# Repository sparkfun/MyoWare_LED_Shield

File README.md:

MyoWare™ LED Shield
========================================

[*MyoWare LED Shield (13688)*](https://www.sparkfun.com/products/13688)

The MyoWare™ LED Shield is designed to pair with the MyoWare™ Muscle Sensor. The 10 segment bar graph shows the magnitude of the measured signal.

Repository Contents
-------------------

* **/Hardware** - Eagle design files (.brd, .sch)

Documentation
--------------
* **[Hookup Guide](https://learn.sparkfun.com/tutorials/myoware-muscle-sensor-kit?_ga=1.172011619.1515819426.1457626448)** - Basic hookup guide for the MyoWare™ LED Shield.
* **[SparkFun Fritzing repo](https://github.com/sparkfun/Fritzing_Parts)** - Fritzing diagrams for SparkFun products.
* **[SparkFun 3D Model repo](https://github.com/sparkfun/3D_Models)** - 3D models of SparkFun products.

License Information
-------------------

This product is _**open source**_!

Please review the LICENSE.md file for license information.

If you have any questions or concerns on licensing, please contact techsupport@sparkfun.com.

Distributed as-is; no warranty is given.

- Your friends at SparkFun.

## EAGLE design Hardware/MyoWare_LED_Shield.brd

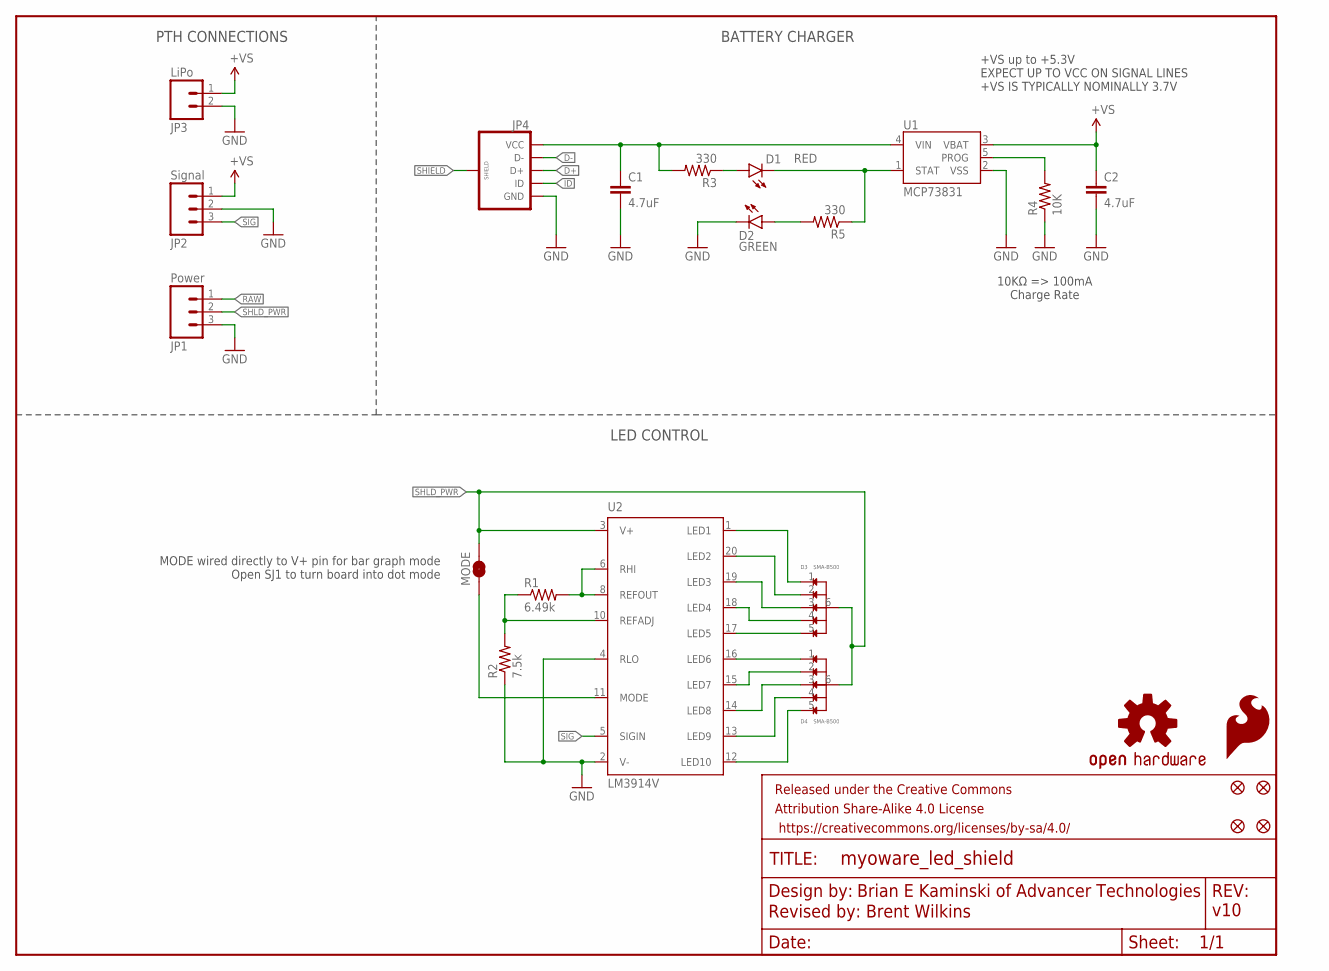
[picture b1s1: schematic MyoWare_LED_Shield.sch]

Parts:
C1, C2: 4.7uF; 0603-CAP
D1: RED; LED-0603
D2: GREEN; LED-0603
D3, D4: SMA-B500; LED_BAR_SMD
FID1, FID2, FID3, FID4: FIDUCIAL1X2; FIDUCIAL-1X2
FRAME1: FRAME-LETTER; CREATIVE_COMMONS
JP1: Power; 1X03_NO_SILK
JP2: Signal; 1X03_NO_SILK
JP3: LiPo; 1X02_NO_SILK
JP4: USB_MICROB_PLUGCONN-11752; USB-B-MICRO-SMD_V03
LOGO1: SFE_LOGO_FLAME.1_INCH; SFE_LOGO_FLAME_.1
LOGO2: OSHW-LOGOS; OSHW-LOGO-S
MODE: JUMPER-PAD-2-NC_BY_TRACE; PAD-JUMPER-2-NC_BY_TRACE_YES_SILK
R1: 6.49k; R0603
R2: 7.5k; R0603
R3, R5: 330; 0603-RES
R4: 10K; 0603-RES
U1: MCP73831; SOT23-5
U2: LM3914V; PLCC20S

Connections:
+VS: C2.1, JP2.1, JP3.1, U1.3 (VBAT)
D+: JP4.D+
D-: JP4.D-
GND: C1.2, C2.2, D2.C, JP1.3, JP2.2, JP3.2, JP4.GND, R2.1, R4.1, U1.2 (VSS), U2.2 (V-), U2.4 (RLO)
ID: JP4.ID
unnamed: D3.1, U2.1 (LED1)
unnamed: D3.2, U2.20 (LED2)
unnamed: D3.5, U2.17 (LED5)
unnamed: D3.3, U2.19 (LED3)
unnamed: D4.1, U2.16 (LED6)
unnamed: MODE.1, U2.11 (MODE)
unnamed: D3.4, U2.18 (LED4)
unnamed: D2.A, R5.2
unnamed: D1.A, R3.1
unnamed: D4.2, U2.15 (LED7)
unnamed: D4.3, U2.14 (LED8)
unnamed: D4.4, U2.13 (LED9)
unnamed: D4.5, U2.12 (LED10)
unnamed: D1.C, R5.1, U1.1 (STAT)
unnamed: R4.2, U1.5 (PROG)
unnamed: R1.1, R2.2, U2.10 (REFADJ)
unnamed: R1.2, U2.6 (RHI), U2.8 (REFOUT)
RAW: JP1.1
SHIELD: JP4.SHIELD1 (SHIELD), JP4.SHIELD2 (SHIELD), JP4.SHIELD3 (SHIELD)
SHLD_PWR: D3.6, D4.6, JP1.2, MODE.2, U2.3 (V+)
SIG: JP2.3, U2.5 (SIGIN)
VBUS: C1.1, JP4.VBUS (VCC), R3.2, U1.4 (VIN)

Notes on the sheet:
Brian E Kaminski of Advancer Technologies
Revised by: Brent Wilkins
v10
+VS up to +5.3V EXPECT UP TO VCC ON SIGNAL LINES +VS IS TYPICALLY NOMINALLY 3.7V
MODE wired directly to V+ pin for bar graph mode Open SJ1 to turn board into dot mode
PTH CONNECTIONS
BATTERY CHARGER
LED CONTROL
10KΩ => 100mA Charge Rate

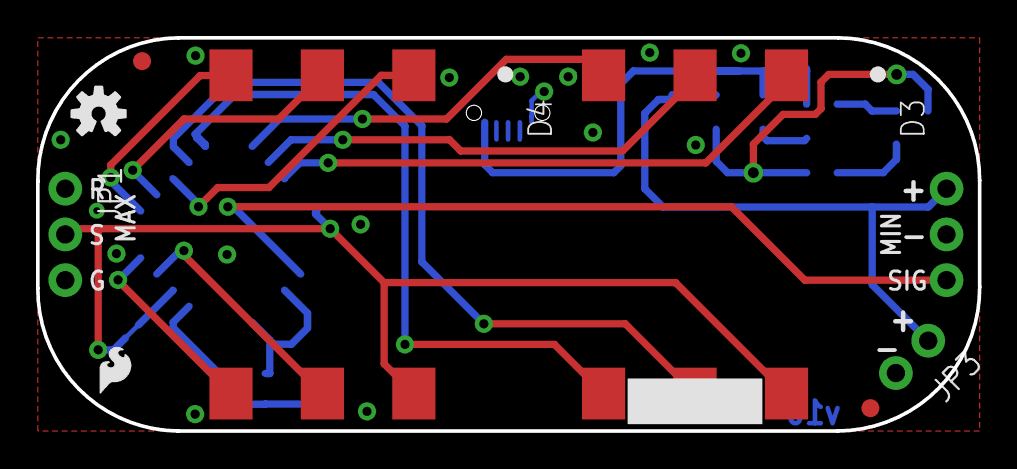
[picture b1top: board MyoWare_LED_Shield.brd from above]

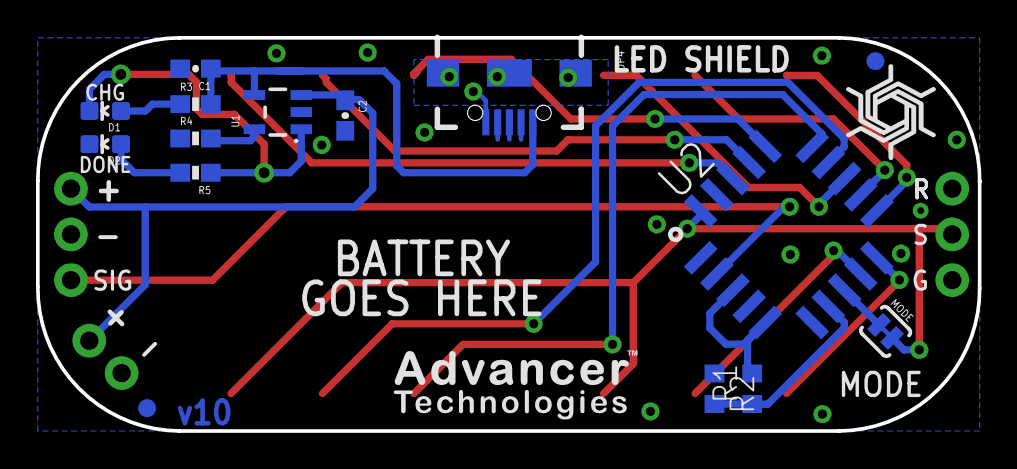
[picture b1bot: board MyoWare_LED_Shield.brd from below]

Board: 2 copper layers, 52.3 x 21.8 mm, 27 parts (17 on the bottom side), 23 nets.

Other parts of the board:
U$6: ADVANCER_LOGO
U$9: SPIRAL_LOGO_60%

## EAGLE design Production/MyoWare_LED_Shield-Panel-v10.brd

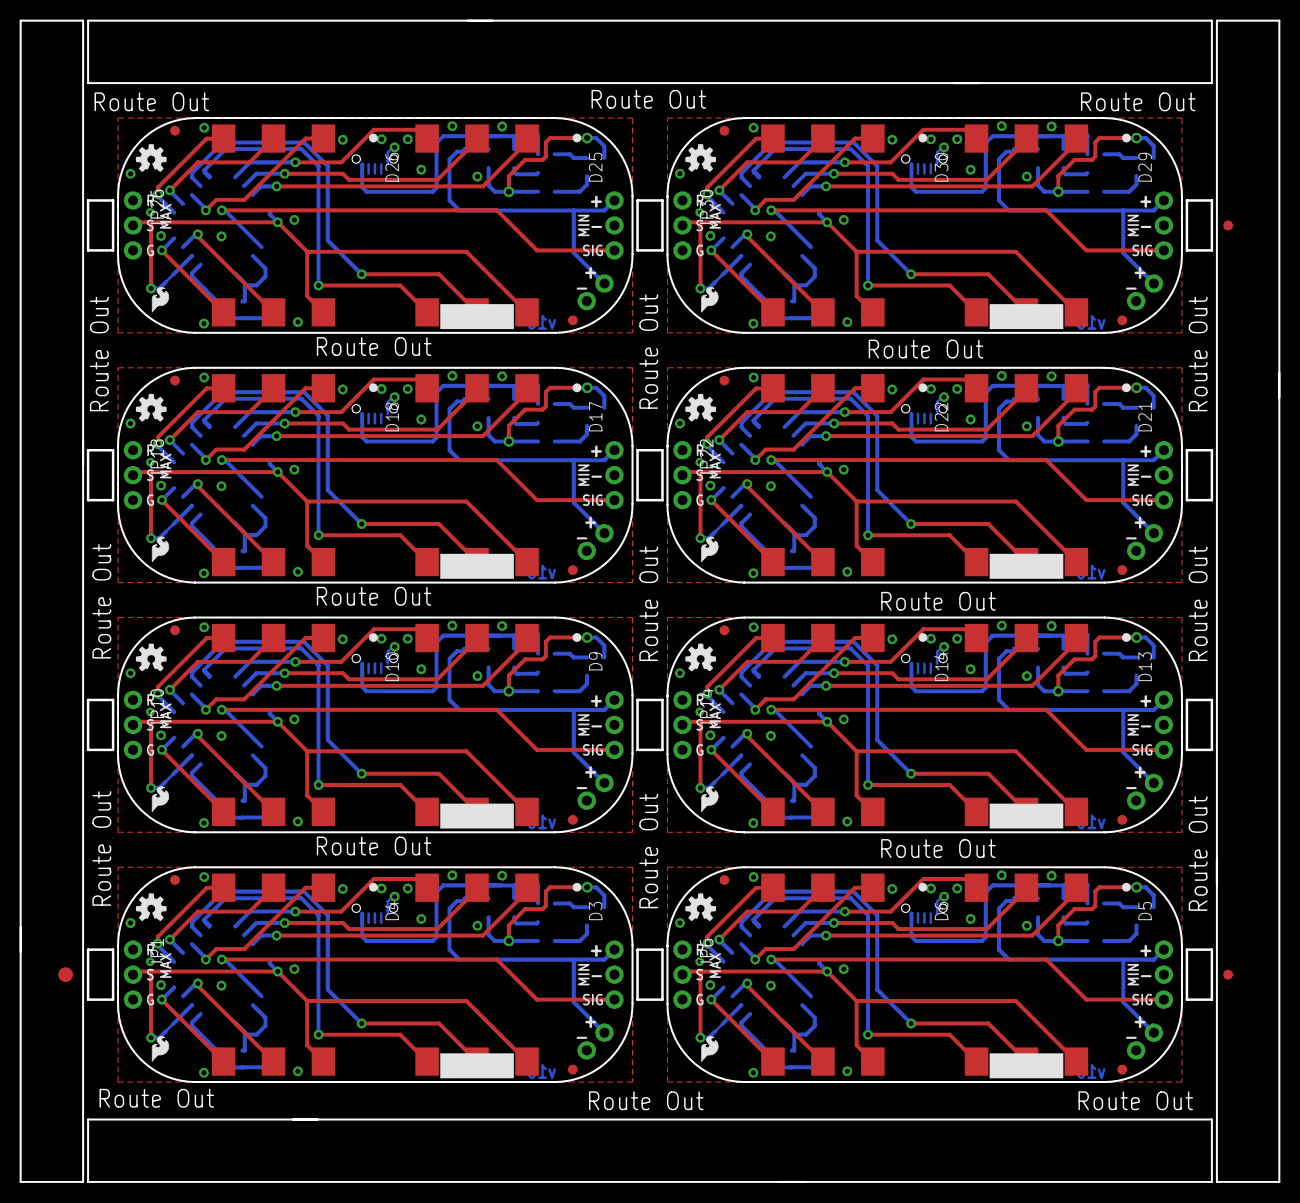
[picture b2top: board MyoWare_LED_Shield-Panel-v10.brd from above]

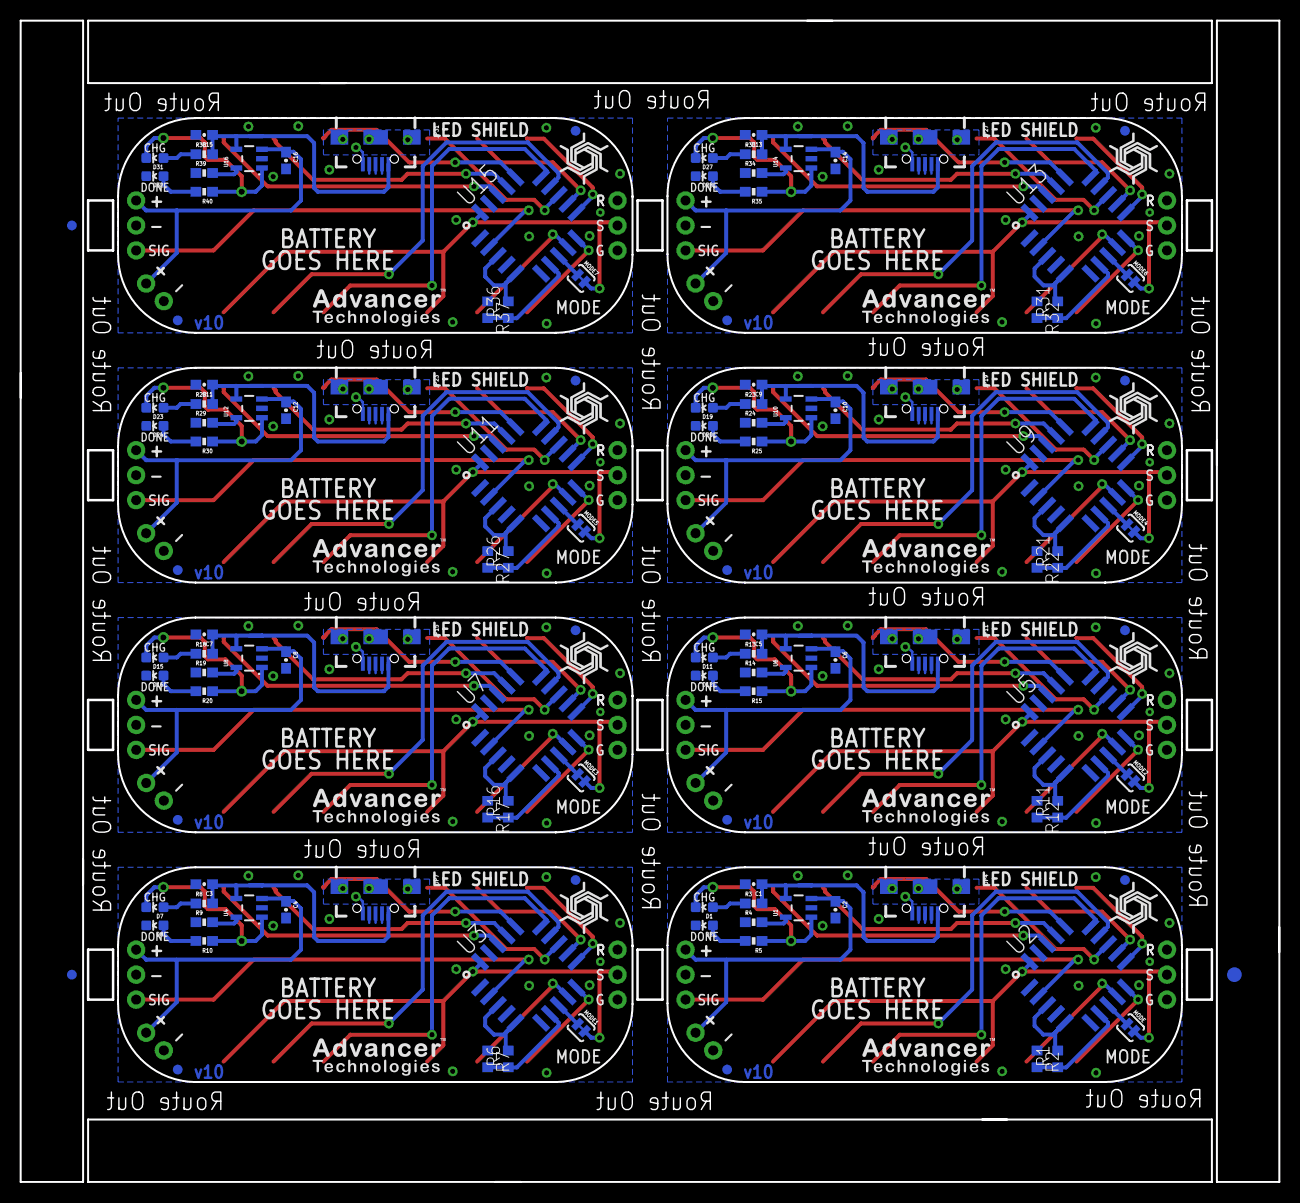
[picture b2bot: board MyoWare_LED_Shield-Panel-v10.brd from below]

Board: 2 copper layers, 128.0 x 118.1 mm, 214 parts (139 on the bottom side), 184 nets.

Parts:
C1, C2, C3, C4, C5, C6, C7, C8, C9, C10, C11, C12, C13, C14, C15, C16: 4.7uF; 0603-CAP
D1, D7, D11, D15, D19, D23, D27, D31: RED; LED-0603
D2, D8, D12, D16, D20, D24, D28, D32: GREEN; LED-0603
D3, D4, D5, D6, D9, D10, D13, D14, D17, D18, D21, D22, D25, D26, D29, D30: SMA-B500; LED_BAR_SMD
E$1, E$4: FIDUCIAL-1.5X3
E$2, E$3, E$5, E$6: FIDUCIAL-1X2
FID1, FID2, FID3, FID4, FID5, FID6, FID7, FID8, FID9, FID10, FID11, FID12, FID13, FID14, FID15, FID16, FID17, FID18, FID19, FID20, FID21, FID22, FID23, FID24, FID25, FID26, FID27, FID28, FID29, FID30, FID31, FID32: FIDUCIAL1X2; FIDUCIAL-1X2
JP1, JP6, JP10, JP14, JP18, JP22, JP26, JP30: Power; 1X03_NO_SILK
JP2, JP5, JP9, JP13, JP17, JP21, JP25, JP29: Signal; 1X03_NO_SILK
JP3, JP8, JP12, JP16, JP20, JP24, JP28, JP32: LiPo; 1X02_NO_SILK
JP4, JP7, JP11, JP15, JP19, JP23, JP27, JP31: USB-B-MICRO-SMD_V03
LOGO1, LOGO3, LOGO5, LOGO7, LOGO9, LOGO11, LOGO13, LOGO15: SFE_LOGO_FLAME.1_INCH; SFE_LOGO_FLAME_.1
LOGO2, LOGO4, LOGO6, LOGO8, LOGO10, LOGO12, LOGO14, LOGO16: OSHW-LOGOS; OSHW-LOGO-S
MODE, MODE1, MODE2, MODE3, MODE4, MODE5, MODE6, MODE7: JUMPER-PAD-2-NC_BY_TRACE; PAD-JUMPER-2-NC_BY_TRACE_YES_SILK
R1, R6, R11, R16, R21, R26, R31, R36: 6.49k; R0603
R2, R7, R12, R17, R22, R27, R32, R37: 7.5k; R0603
R3, R5, R8, R10, R13, R15, R18, R20, R23, R25, R28, R30, R33, R35, R38, R40: 330; 0603-RES
R4, R9, R14, R19, R24, R29, R34, R39: 10K; 0603-RES
U1, U4, U6, U8, U10, U12, U14, U16: MCP73831; SOT23-5
U2, U3, U5, U7, U9, U11, U13, U15: LM3914V; PLCC20S
U$1, U$3, U$5, U$8, U$9, U$11, U$13, U$15: SPIRAL_LOGO_60%
U$2, U$4, U$6, U$7, U$10, U$12, U$14, U$16: ADVANCER_LOGO

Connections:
+VS: C2.1, JP2.1, JP3.1, U1.3
+VS1: C4.1, JP5.1, JP8.1, U4.3
+VS2: C6.1, JP9.1, JP12.1, U6.3
+VS3: C8.1, JP13.1, JP16.1, U8.3
+VS4: C10.1, JP17.1, JP20.1, U10.3
+VS5: C12.1, JP21.1, JP24.1, U12.3
+VS6: C14.1, JP25.1, JP28.1, U14.3
+VS7: C16.1, JP29.1, JP32.1, U16.3
GND: C1.2, C2.2, D2.C, JP1.3, JP2.2, JP3.2, JP4.GND, R2.1, R4.1, U1.2, U2.2, U2.4
GND1: C3.2, C4.2, D8.C, JP5.2, JP6.3, JP7.GND, JP8.2, R7.1, R9.1, U3.2, U3.4, U4.2
GND2: C5.2, C6.2, D12.C, JP9.2, JP10.3, JP11.GND, JP12.2, R12.1, R14.1, U5.2, U5.4, U6.2
GND3: C7.2, C8.2, D16.C, JP13.2, JP14.3, JP15.GND, JP16.2, R17.1, R19.1, U7.2, U7.4, U8.2
GND4: C9.2, C10.2, D20.C, JP17.2, JP18.3, JP19.GND, JP20.2, R22.1, R24.1, U9.2, U9.4, U10.2
GND5: C11.2, C12.2, D24.C, JP21.2, JP22.3, JP23.GND, JP24.2, R27.1, R29.1, U11.2, U11.4, U12.2
GND6: C13.2, C14.2, D28.C, JP25.2, JP26.3, JP27.GND, JP28.2, R32.1, R34.1, U13.2, U13.4, U14.2
GND7: C15.2, C16.2, D32.C, JP29.2, JP30.3, JP31.GND, JP32.2, R37.1, R39.1, U15.2, U15.4, U16.2
unnamed: D3.1, U2.1
unnamed: D3.2, U2.20
unnamed: D3.5, U2.17
unnamed: D3.3, U2.19
unnamed: D4.1, U2.16
unnamed: MODE.1, U2.11
unnamed: D5.1, U3.1
unnamed: D3.4, U2.18
unnamed: D2.A, R5.2
unnamed: D1.A, R3.1
unnamed: D4.2, U2.15
unnamed: D4.3, U2.14
unnamed: D4.4, U2.13
unnamed: D4.5, U2.12
unnamed: D1.C, R5.1, U1.1
unnamed: D5.2, U3.20
unnamed: R4.2, U1.5
unnamed: D5.3, U3.19
unnamed: R1.1, R2.2, U2.10
unnamed: R1.2, U2.6, U2.8
unnamed: D5.4, U3.18
unnamed: D6.2, U3.15
unnamed: D6.3, U3.14
unnamed: D6.4, U3.13
unnamed: D6.5, U3.12
unnamed: R6.1, R7.2, U3.10
unnamed: R6.2, U3.6, U3.8
unnamed: D5.5, U3.17
unnamed: D6.1, U3.16
unnamed: MODE1.1, U3.11
unnamed: D7.A, R8.1
unnamed: D7.C, R10.1, U4.1
unnamed: R9.2, U4.5
unnamed: D8.A, R10.2
unnamed: D9.1, U5.1
unnamed: D9.2, U5.20
unnamed: D9.3, U5.19
unnamed: D9.4, U5.18
unnamed: D10.2, U5.15
unnamed: D10.3, U5.14
unnamed: D10.4, U5.13
unnamed: D10.5, U5.12
unnamed: R11.1, R12.2, U5.10
unnamed: R11.2, U5.6, U5.8
unnamed: D9.5, U5.17
unnamed: D10.1, U5.16
unnamed: MODE2.1, U5.11
unnamed: D11.A, R13.1
unnamed: D11.C, R15.1, U6.1
unnamed: R14.2, U6.5
unnamed: D12.A, R15.2
unnamed: D13.1, U7.1
unnamed: D13.2, U7.20
unnamed: D13.3, U7.19
unnamed: D13.4, U7.18
unnamed: D14.2, U7.15
unnamed: D14.3, U7.14
unnamed: D14.4, U7.13
unnamed: D14.5, U7.12
unnamed: R16.1, R17.2, U7.10
unnamed: R16.2, U7.6, U7.8
unnamed: D13.5, U7.17
unnamed: D14.1, U7.16
unnamed: MODE3.1, U7.11
unnamed: D15.A, R18.1
unnamed: D15.C, R20.1, U8.1
unnamed: R19.2, U8.5
unnamed: D16.A, R20.2
unnamed: D17.1, U9.1
unnamed: D17.2, U9.20
unnamed: D17.3, U9.19
unnamed: D17.4, U9.18
unnamed: D18.2, U9.15
unnamed: D18.3, U9.14
unnamed: D18.4, U9.13
unnamed: D18.5, U9.12
unnamed: R21.1, R22.2, U9.10
unnamed: R21.2, U9.6, U9.8
unnamed: D17.5, U9.17
unnamed: D18.1, U9.16
unnamed: MODE4.1, U9.11
unnamed: D19.A, R23.1
unnamed: D19.C, R25.1, U10.1
unnamed: R24.2, U10.5
unnamed: D20.A, R25.2
unnamed: D21.1, U11.1
unnamed: D21.2, U11.20
unnamed: D21.3, U11.19
unnamed: D21.4, U11.18
unnamed: D22.2, U11.15
unnamed: D22.3, U11.14
unnamed: D22.4, U11.13
unnamed: D22.5, U11.12
unnamed: R26.1, R27.2, U11.10
unnamed: R26.2, U11.6, U11.8
unnamed: D21.5, U11.17
unnamed: D22.1, U11.16
unnamed: MODE5.1, U11.11
unnamed: D23.A, R28.1
unnamed: D23.C, R30.1, U12.1
unnamed: R29.2, U12.5
unnamed: D24.A, R30.2
unnamed: D25.1, U13.1
unnamed: D25.2, U13.20
unnamed: D25.3, U13.19
unnamed: D25.4, U13.18
unnamed: D26.2, U13.15
unnamed: D26.3, U13.14
unnamed: D26.4, U13.13
unnamed: D26.5, U13.12
unnamed: R31.1, R32.2, U13.10
unnamed: R31.2, U13.6, U13.8
unnamed: D25.5, U13.17
unnamed: D26.1, U13.16
unnamed: MODE6.1, U13.11
unnamed: D27.A, R33.1
unnamed: D27.C, R35.1, U14.1
unnamed: R34.2, U14.5
unnamed: D28.A, R35.2
unnamed: D29.1, U15.1
unnamed: D29.2, U15.20
unnamed: D29.3, U15.19
unnamed: D29.4, U15.18
unnamed: D30.2, U15.15
unnamed: D30.3, U15.14
unnamed: D30.4, U15.13
unnamed: D30.5, U15.12
unnamed: R36.1, R37.2, U15.10
unnamed: R36.2, U15.6, U15.8
unnamed: D29.5, U15.17
unnamed: D30.1, U15.16
unnamed: MODE7.1, U15.11
unnamed: D31.A, R38.1
unnamed: D31.C, R40.1, U16.1
unnamed: R39.2, U16.5
unnamed: D32.A, R40.2
SHIELD: JP4.SHIELD1, JP4.SHIELD2, JP4.SHIELD3
SHIELD1: JP7.SHIELD1, JP7.SHIELD2, JP7.SHIELD3
SHIELD2: JP11.SHIELD1, JP11.SHIELD2, JP11.SHIELD3
SHIELD3: JP15.SHIELD1, JP15.SHIELD2, JP15.SHIELD3
SHIELD4: JP19.SHIELD1, JP19.SHIELD2, JP19.SHIELD3
SHIELD5: JP23.SHIELD1, JP23.SHIELD2, JP23.SHIELD3
SHIELD6: JP27.SHIELD1, JP27.SHIELD2, JP27.SHIELD3
SHIELD7: JP31.SHIELD1, JP31.SHIELD2, JP31.SHIELD3
SHLD_PWR: D3.6, D4.6, JP1.2, MODE.2, U2.3
SHLD_PWR1: D5.6, D6.6, JP6.2, MODE1.2, U3.3
SHLD_PWR2: D9.6, D10.6, JP10.2, MODE2.2, U5.3
SHLD_PWR3: D13.6, D14.6, JP14.2, MODE3.2, U7.3
SHLD_PWR4: D17.6, D18.6, JP18.2, MODE4.2, U9.3
SHLD_PWR5: D21.6, D22.6, JP22.2, MODE5.2, U11.3
SHLD_PWR6: D25.6, D26.6, JP26.2, MODE6.2, U13.3
SHLD_PWR7: D29.6, D30.6, JP30.2, MODE7.2, U15.3
SIG: JP2.3, U2.5
SIG1: JP5.3, U3.5
SIG2: JP9.3, U5.5
SIG3: JP13.3, U7.5
SIG4: JP17.3, U9.5
SIG5: JP21.3, U11.5
SIG6: JP25.3, U13.5
SIG7: JP29.3, U15.5
VBUS: C1.1, JP4.VBUS, R3.2, U1.4
VBUS1: C3.1, JP7.VBUS, R8.2, U4.4
VBUS2: C5.1, JP11.VBUS, R13.2, U6.4
VBUS3: C7.1, JP15.VBUS, R18.2, U8.4
VBUS4: C9.1, JP19.VBUS, R23.2, U10.4
VBUS5: C11.1, JP23.VBUS, R28.2, U12.4
VBUS6: C13.1, JP27.VBUS, R33.2, U14.4
VBUS7: C15.1, JP31.VBUS, R38.2, U16.4

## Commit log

2015-07-27 Added prod_id to LEDs
2015-07-27 Cosmetic tweaks
2015-11-16 Started move to LiPo based design
2015-11-16 Design rules checked
2015-11-16 Adjusted max +VS
2015-11-16 Tweaks (mostly silk and info)
2015-11-17 Moved the USB jack to board edge to prevent interference with part flair
2016-03-02 Moved charge LEDs to back of board from easier manufacturing
2016-03-03 Added cable header alignment in silk & minor weaks.
2016-03-03 Improved micro-B DFM & fixed alignment silk
2016-03-04 Resolved issue #8 and isuue #9
2016-03-04 Change charge done LED to green
2016-03-09 created panel v10
2016-08-23 MyoWare ReadMe File Update

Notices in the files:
parts and their libraries:
SparkFun-Connectors: Licensing: CC v3.0 Share-Alike You are welcome to use this library for commercial purposes.
SparkFun-Aesthetics: Licensing: Creative Commons ShareAlike 4.0 International - https://creativecommons.org/licenses/by-sa/4.0
SparkFun-Aesthetics: Released under the Creative Commons
